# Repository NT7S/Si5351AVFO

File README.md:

# Si5351AVFO
Si5351A VFO board for the Si5351 Field Manual (Chapter 6).

## Regenerating docs

After any schematic change, run `tools/export_docs.sh` (needs KiCad 10 `kicad-cli`).
It rewrites `docs/Si5351AVFO_schematic.pdf`, the netlist, SVGs and `docs/erc.rpt`.

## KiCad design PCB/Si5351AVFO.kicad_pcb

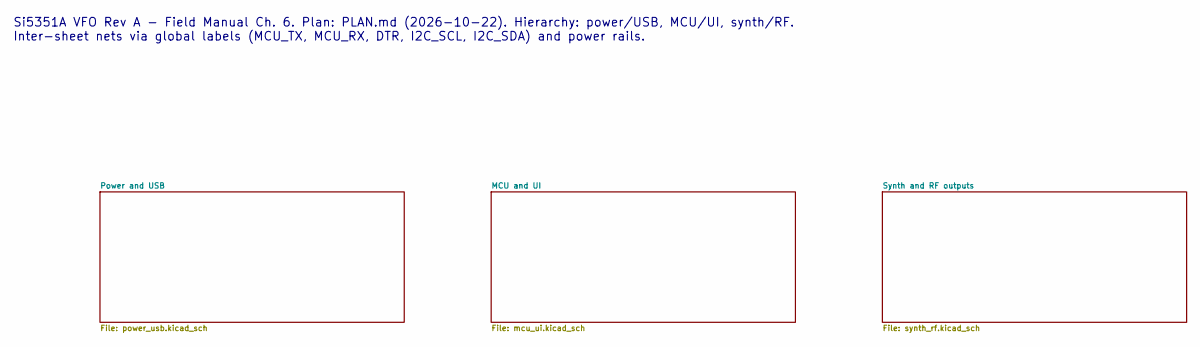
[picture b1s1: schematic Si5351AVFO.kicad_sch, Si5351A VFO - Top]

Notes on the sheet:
Si5351A VFO Rev A - Field Manual Ch. 6. Plan: PLAN.md (2026-10-22). Hierarchy: power/USB, MCU/UI, synth/RF. Inter-sheet nets via global labels (MCU_TX, MCU_RX, DTR, I2C_SCL, I2C_SDA) and power rails.

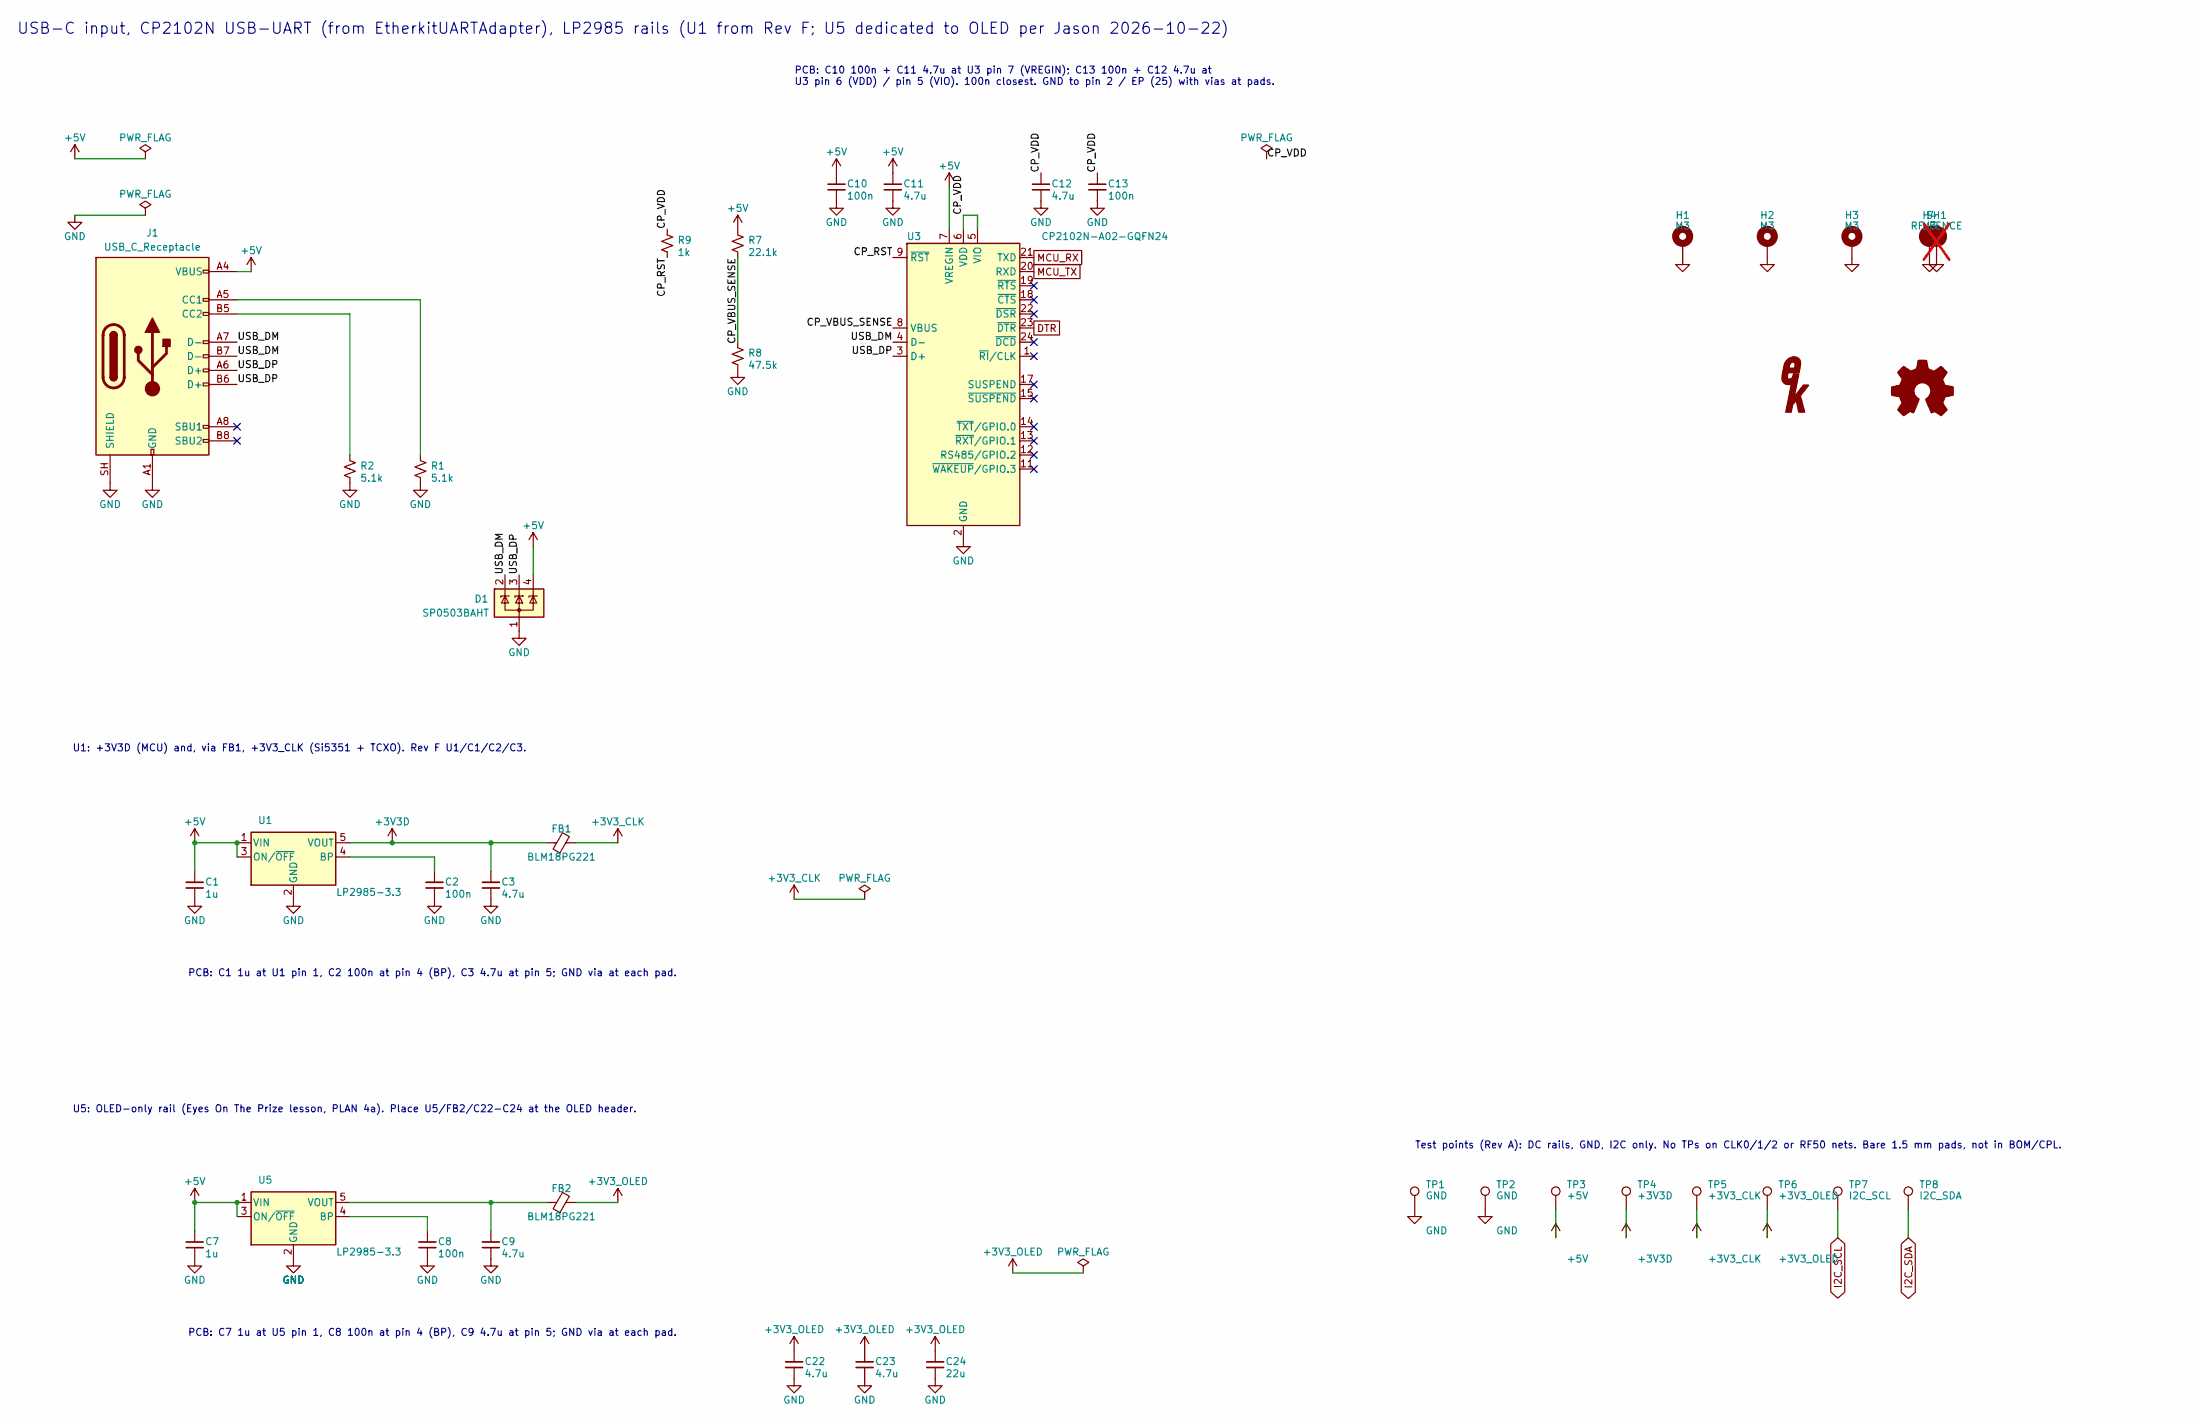
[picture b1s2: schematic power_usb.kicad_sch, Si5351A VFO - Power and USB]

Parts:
C1, C7: 1u; C_0805_2012Metric; MPN CL21B105KBFNNNE; LCSC C28323
C2, C8: 100n; C_0805_2012Metric; MPN CC0805KRX7R9BB104; LCSC C49678
C3, C9, C22, C23: 4.7u; C_0805_2012Metric; MPN CL21A475KAQNNNE; LCSC C1779
C10, C13: 100n; C_0603_1608Metric; MPN CC0603KRX7R9BB104; LCSC C14663
C11, C12: 4.7u; C_0603_1608Metric; MPN CL10A475KO8NNNC; LCSC C19666
C24: 22u; C_1206_3216Metric; MPN CL31A226KAHNNNE; LCSC C12891
D1: SP0503BAHT; SOT-143; MPN SP0503BAHTG; LCSC C7074
FB1, FB2: BLM18PG221; L_0603_1608Metric; MPN BLM18PG221SN1D; LCSC C80165
H1, H2, H3, H4: M3; MountingHole_3.2mm_M3_Pad_Via
J1: USB_C_Receptacle; USB_C_Receptacle_HCTL_HC-TYPE-C-16P-01A; MPN HC-TYPE-C-16P-01A; LCSC C2894897
R1, R2: 5.1k; R_0603_1608Metric; MPN 0603WAF5101T5E; LCSC C23186
R7: 22.1k; R_0603_1608Metric; MPN RC0603FR-0722K1L; LCSC C137768
R8: 47.5k; R_0603_1608Metric; MPN FRC0603F4752TS; LCSC C2933225
R9: 1k; R_0603_1608Metric; MPN 0603WAF1001T5E; LCSC C21190
SH1: RF_FENCE; RF_Fence_42x33.5mm; not fitted
TP1, TP2: GND; TestPoint_Pad_D1.5mm
TP3: +5V; TestPoint_Pad_D1.5mm
TP4: +3V3D; TestPoint_Pad_D1.5mm
TP5: +3V3_CLK; TestPoint_Pad_D1.5mm
TP6: +3V3_OLED; TestPoint_Pad_D1.5mm
TP7: I2C_SCL; TestPoint_Pad_D1.5mm
TP8: I2C_SDA; TestPoint_Pad_D1.5mm
U1, U5: LP2985-3.3; SOT-23-5; MPN LP2985AIM5-3.3/NOPB; LCSC C16085
U3: CP2102N-A02-GQFN24; QFN-24-1EP_4x4mm_P0.5mm_EP2.6x2.6mm; MPN CP2102N-A02-GQFN24R; LCSC C969151

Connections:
+3V3D: C3.1, FB1.1, TP4.1, U1.5 (VOUT); also elsewhere on the board
+3V3_CLK: FB1.2, TP5.1; also elsewhere on the board
+3V3_OLED: C22.1, C23.1, C24.1, FB2.2, TP6.1; also elsewhere on the board
+5V: C1.1, C7.1, C10.1, C11.1, D1.4 (K), J1.A4 (VBUS), J1.A9 (VBUS), J1.B4 (VBUS), J1.B9 (VBUS), R7.1, TP3.1, U1.1 (VIN), U1.3 (ON/~OFF), U3.7 (VREGIN), U5.1 (VIN), U5.3 (ON/~OFF)
/Power and USB/CP_RST: R9.2, U3.9 (~RST)
/Power and USB/CP_VBUS_SENSE: R7.2, R8.1, U3.8 (VBUS)
/Power and USB/CP_VDD: C12.1, C13.1, R9.1, U3.5 (VIO), U3.6 (VDD)
/Power and USB/USB_DM: D1.2 (K), J1.A7 (D-), J1.B7 (D-), U3.4 (D-)
/Power and USB/USB_DP: D1.3 (K), J1.A6 (D+), J1.B6 (D+), U3.3 (D+)
DTR: U3.23 (~DTR); also elsewhere on the board
GND: C1.2, C2.2, C3.2, C7.2, C8.2, C9.2, C10.2, C11.2, C12.2, C13.2, C22.2, C23.2, C24.2, D1.1 (A), H1.1, H2.1, H3.1, H4.1, J1.A1 (GND), J1.A12 (GND), J1.B1 (GND), J1.B12 (GND), J1.SH (SHIELD), R1.2, R2.2, R8.2, SH1.1, TP1.1, TP2.1, U1.2 (GND), U3.2 (GND), U3.25 (GND), U5.2 (GND); also elsewhere on the board
I2C_SCL: TP7.1; also elsewhere on the board
I2C_SDA: TP8.1; also elsewhere on the board
MCU_RX: U3.21 (TXD); also elsewhere on the board
MCU_TX: U3.20 (RXD); also elsewhere on the board
unnamed: J1.A5 (CC1), R1.1
unnamed: J1.B5 (CC2), R2.1
unnamed: C2.1, U1.4 (BP)
unnamed: C8.1, U5.4 (BP)
unnamed: C9.1, FB2.1, U5.5 (VOUT)

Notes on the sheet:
U1: +3V3D (MCU) and, via FB1, +3V3_CLK (Si5351 + TCXO). Rev F U1/C1/C2/C3.
USB-C input, CP2102N USB-UART (from EtherkitUARTAdapter), LP2985 rails (U1 from Rev F; U5 dedicated to OLED per Jason 2026-10-22)
U5: OLED-only rail (Eyes On The Prize lesson, PLAN 4a). Place U5/FB2/C22-C24 at the OLED header.
PCB: C10 100n + C11 4.7u at U3 pin 7 (VREGIN); C13 100n + C12 4.7u at U3 pin 6 (VDD) / pin 5 (VIO). 100n closest. GND to pin 2 / EP (25) with vias at pads.
PCB: C1 1u at U1 pin 1, C2 100n at pin 4 (BP), C3 4.7u at pin 5; GND via at each pad.
PCB: C7 1u at U5 pin 1, C8 100n at pin 4 (BP), C9 4.7u at pin 5; GND via at each pad.
Test points (Rev A): DC rails, GND, I2C only. No TPs on CLK0/1/2 or RF50 nets. Bare 1.5 mm pads, not in BOM/CPL.

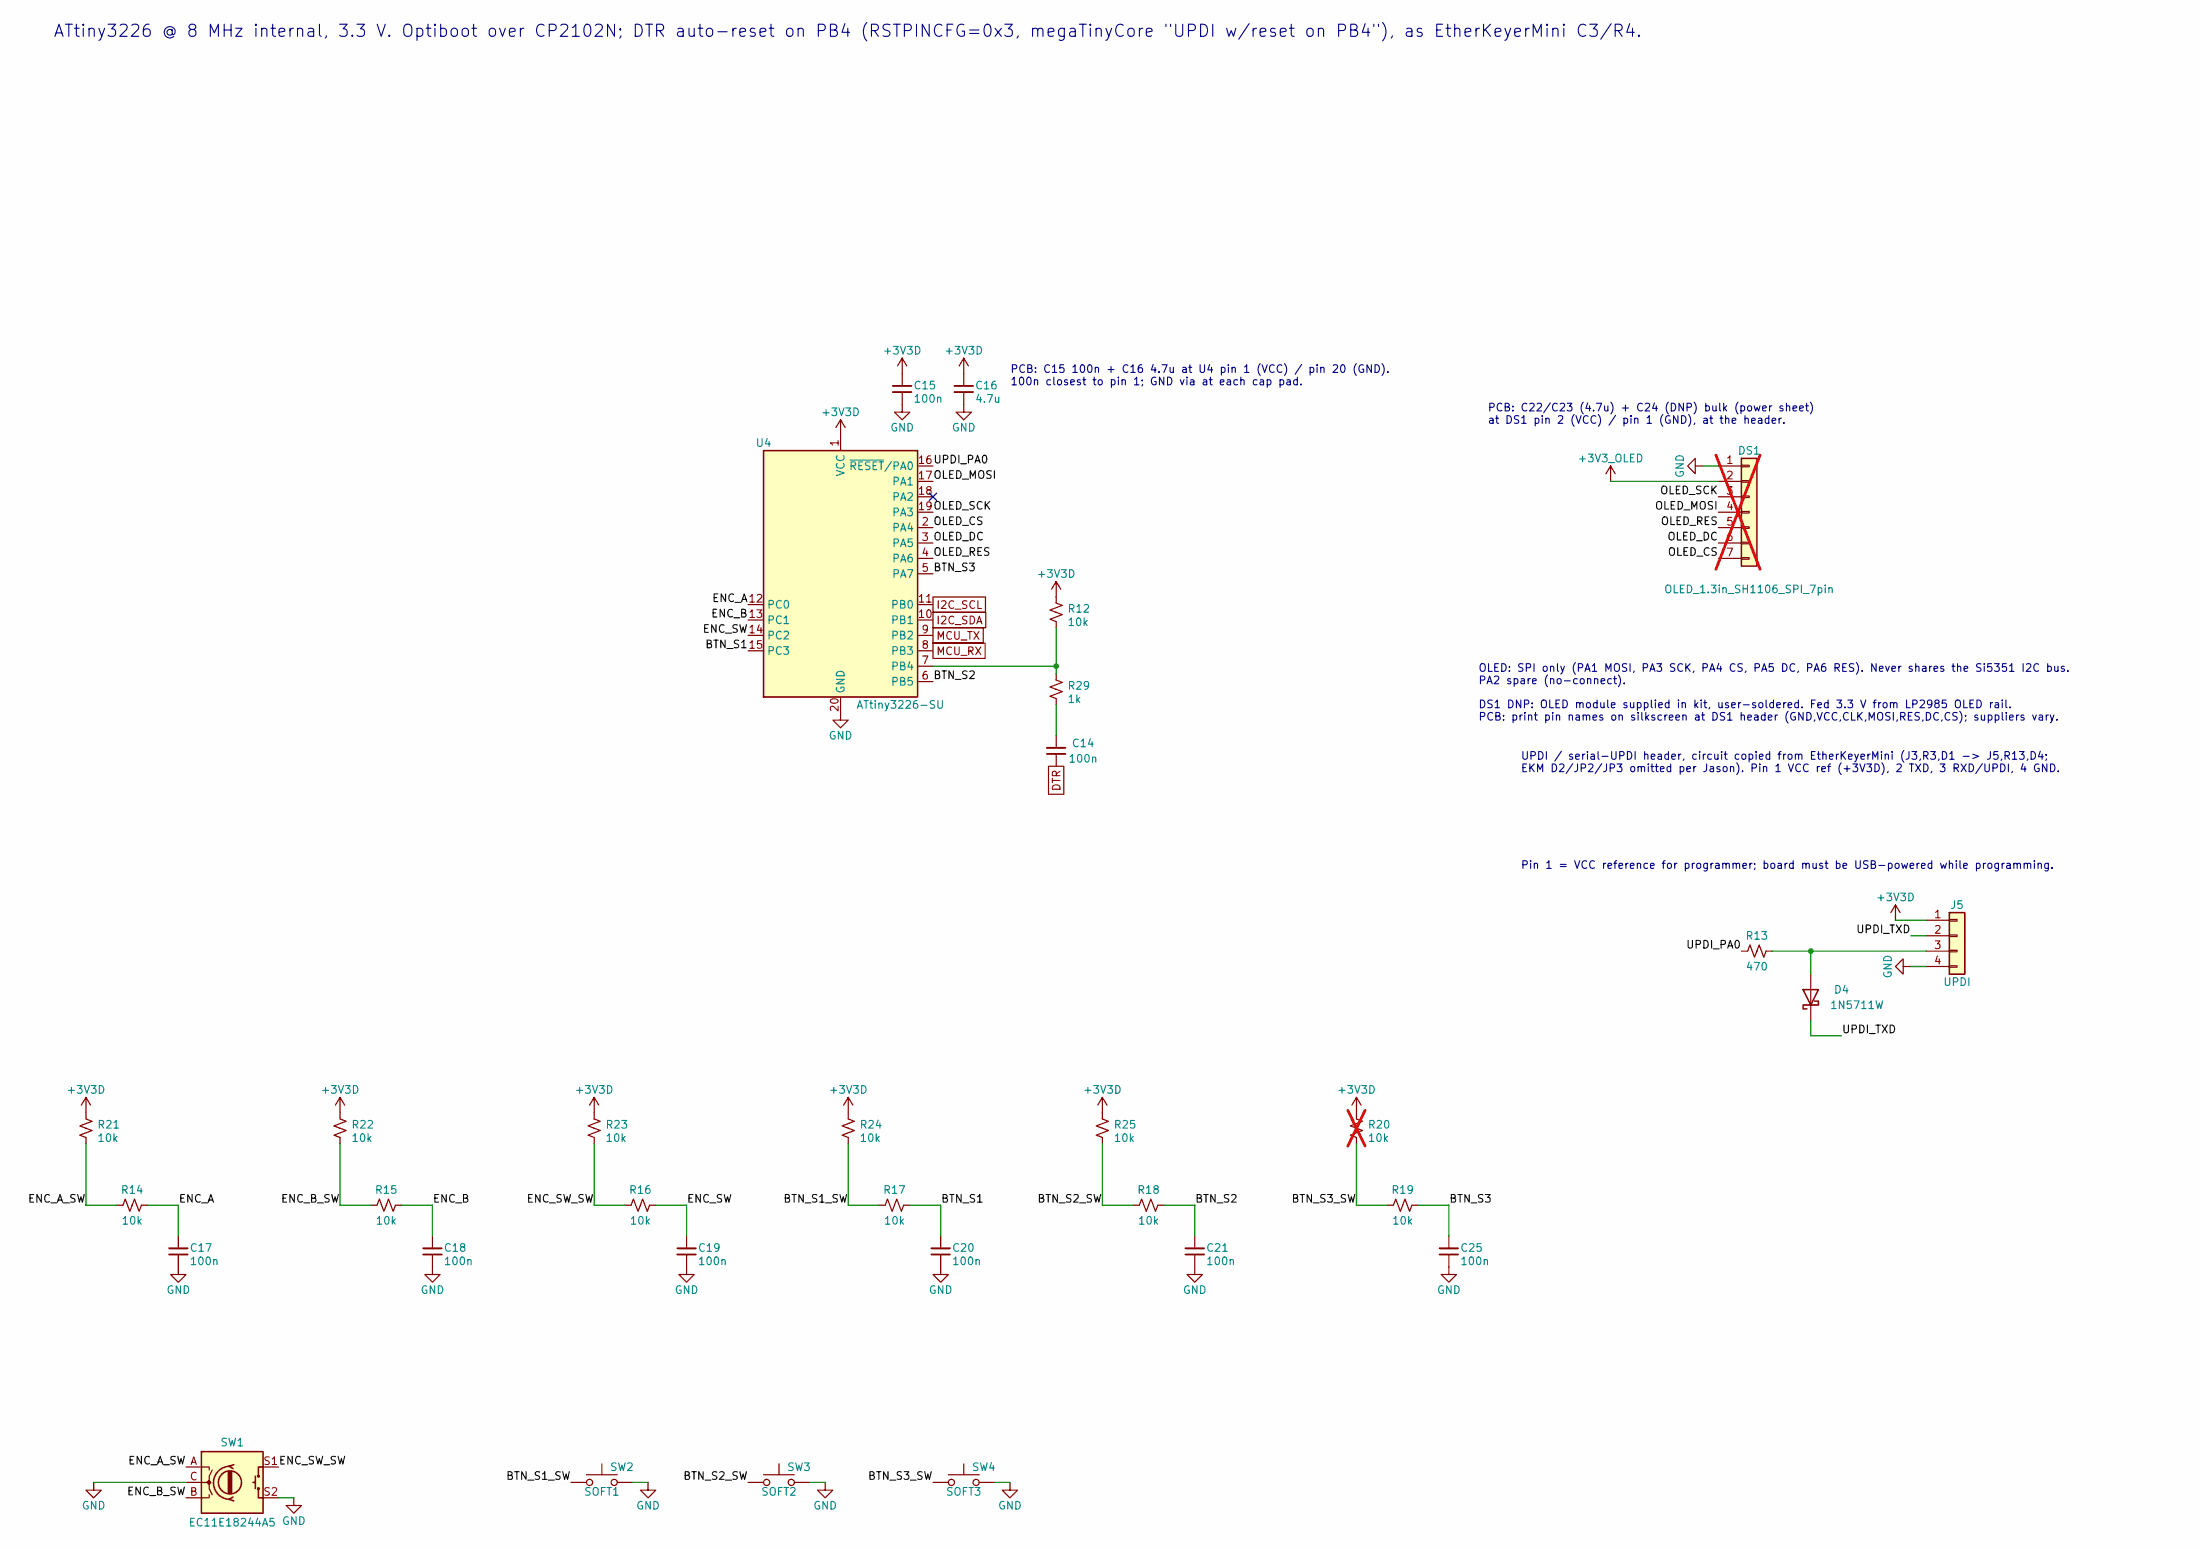
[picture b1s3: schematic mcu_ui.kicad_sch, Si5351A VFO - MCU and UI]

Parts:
C14, C15, C17, C18, C19, C20, C21, C25: 100n; C_0805_2012Metric; MPN CC0805KRX7R9BB104; LCSC C49678
C16: 4.7u; C_0805_2012Metric; MPN CL21A475KAQNNNE; LCSC C1779
D4: 1N5711W; D_SOD-123; MPN 1N5711W-7-F; LCSC C154843
DS1: OLED_1.3in_SH1106_SPI_7pin; PinHeader_1x07_P2.54mm_Vertical; MPN generic 1.3in SH1106 SPI 7-pin; not fitted
J5: UPDI; PinHeader_1x04_P2.54mm_Vertical; MPN B-2100S04P-A110; LCSC C124378
R12, R14, R15, R16, R17, R18, R19, R21, R22, R23, R24, R25: 10k; R_0805_2012Metric; MPN 0805W8F1002T5E; LCSC C17414
R13: 470; R_0603_1608Metric; MPN 0603WAF4700T5E; LCSC C23179
R20: 10k; R_0805_2012Metric; MPN 0805W8F1002T5E; LCSC C17414; not fitted
R29: 1k; R_0603_1608Metric; MPN 0603WAF1001T5E; LCSC C21190
SW1: EC11E18244A5; RotaryEncoder_Alps_EC11E-Switch_Vertical_H20mm; MPN EC11E18244A5; LCSC C255515
SW2: SOFT1; SW_Push_6x6mm_SMD_KH-6X6X11H-STM; MPN KH-6X6X11H-STM; LCSC C2837537
SW3: SOFT2; SW_Push_6x6mm_SMD_KH-6X6X11H-STM; MPN KH-6X6X11H-STM; LCSC C2837537
SW4: SOFT3; SW_Push_6x6mm_SMD_KH-6X6X11H-STM; MPN KH-6X6X11H-STM; LCSC C2837537
U4: ATtiny3226-SU; SOIC-20W_7.5x12.8mm_P1.27mm; MPN ATTINY3226-SU; LCSC C3234898

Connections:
+3V3D: C15.1, C16.1, J5.1, R12.1, R20.1, R21.1, R22.1, R23.1, R24.1, R25.1, U4.1 (VCC); also elsewhere on the board
+3V3_OLED: DS1.2; also elsewhere on the board
/MCU and UI/BTN_S1: C20.1, R17.2, U4.15 (PC3)
/MCU and UI/BTN_S1_SW: R17.1, R24.2, SW2.1
/MCU and UI/BTN_S2: C21.1, R18.2, U4.6 (PB5)
/MCU and UI/BTN_S2_SW: R18.1, R25.2, SW3.1
/MCU and UI/BTN_S3: C25.1, R19.2, U4.5 (PA7)
/MCU and UI/BTN_S3_SW: R19.1, R20.2, SW4.1
/MCU and UI/ENC_A: C17.1, R14.2, U4.12 (PC0)
/MCU and UI/ENC_A_SW: R14.1, R21.2, SW1.A
/MCU and UI/ENC_B: C18.1, R15.2, U4.13 (PC1)
/MCU and UI/ENC_B_SW: R15.1, R22.2, SW1.B
/MCU and UI/ENC_SW: C19.1, R16.2, U4.14 (PC2)
/MCU and UI/ENC_SW_SW: R16.1, R23.2, SW1.S1
/MCU and UI/OLED_CS: DS1.7, U4.2 (PA4)
/MCU and UI/OLED_DC: DS1.6, U4.3 (PA5)
/MCU and UI/OLED_MOSI: DS1.4, U4.17 (PA1)
/MCU and UI/OLED_RES: DS1.5, U4.4 (PA6)
/MCU and UI/OLED_SCK: DS1.3, U4.19 (PA3)
/MCU and UI/UPDI_PA0: R13.1, U4.16 (~RESET/PA0)
/MCU and UI/UPDI_TXD: D4.1 (K), J5.2
DTR: C14.1; also elsewhere on the board
GND: C15.2, C16.2, C17.2, C18.2, C19.2, C20.2, C21.2, C25.2, DS1.1, J5.4, SW1.C, SW1.S2, SW2.2, SW3.2, SW4.2, U4.20 (GND); also elsewhere on the board
I2C_SCL: U4.11 (PB0); also elsewhere on the board
I2C_SDA: U4.10 (PB1); also elsewhere on the board
MCU_RX: U4.8 (PB3); also elsewhere on the board
MCU_TX: U4.9 (PB2); also elsewhere on the board
unnamed: C14.2, R29.2
unnamed: D4.2 (A), J5.3, R13.2
unnamed: R12.2, R29.1, U4.7 (PB4)

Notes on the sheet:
UPDI / serial-UPDI header, circuit copied from EtherKeyerMini (J3,R3,D1 -> J5,R13,D4; EKM D2/JP2/JP3 omitted per Jason). Pin 1 VCC ref (+3V3D), 2 TXD, 3 RXD/UPDI, 4 GND.
OLED: SPI only (PA1 MOSI, PA3 SCK, PA4 CS, PA5 DC, PA6 RES). Never shares the Si5351 I2C bus. PA2 spare (no-connect).
DS1 DNP: OLED module supplied in kit, user-soldered. Fed 3.3 V from LP2985 OLED rail. PCB: print pin names on silkscreen at DS1 header (GND,VCC,CLK,MOSI,RES,DC,CS); suppliers vary.
ATtiny3226 @ 8 MHz internal, 3.3 V. Optiboot over CP2102N; DTR auto-reset on PB4 (RSTPINCFG=0x3, megaTinyCore "UPDI w/reset on PB4"), as EtherKeyerMini C3/R4.
Pin 1 = VCC reference for programmer; board must be USB-powered while programming.
PCB: C15 100n + C16 4.7u at U4 pin 1 (VCC) / pin 20 (GND). 100n closest to pin 1; GND via at each cap pad.
PCB: C22/C23 (4.7u) + C24 (DNP) bulk (power sheet) at DS1 pin 2 (VCC) / pin 1 (GND), at the header.

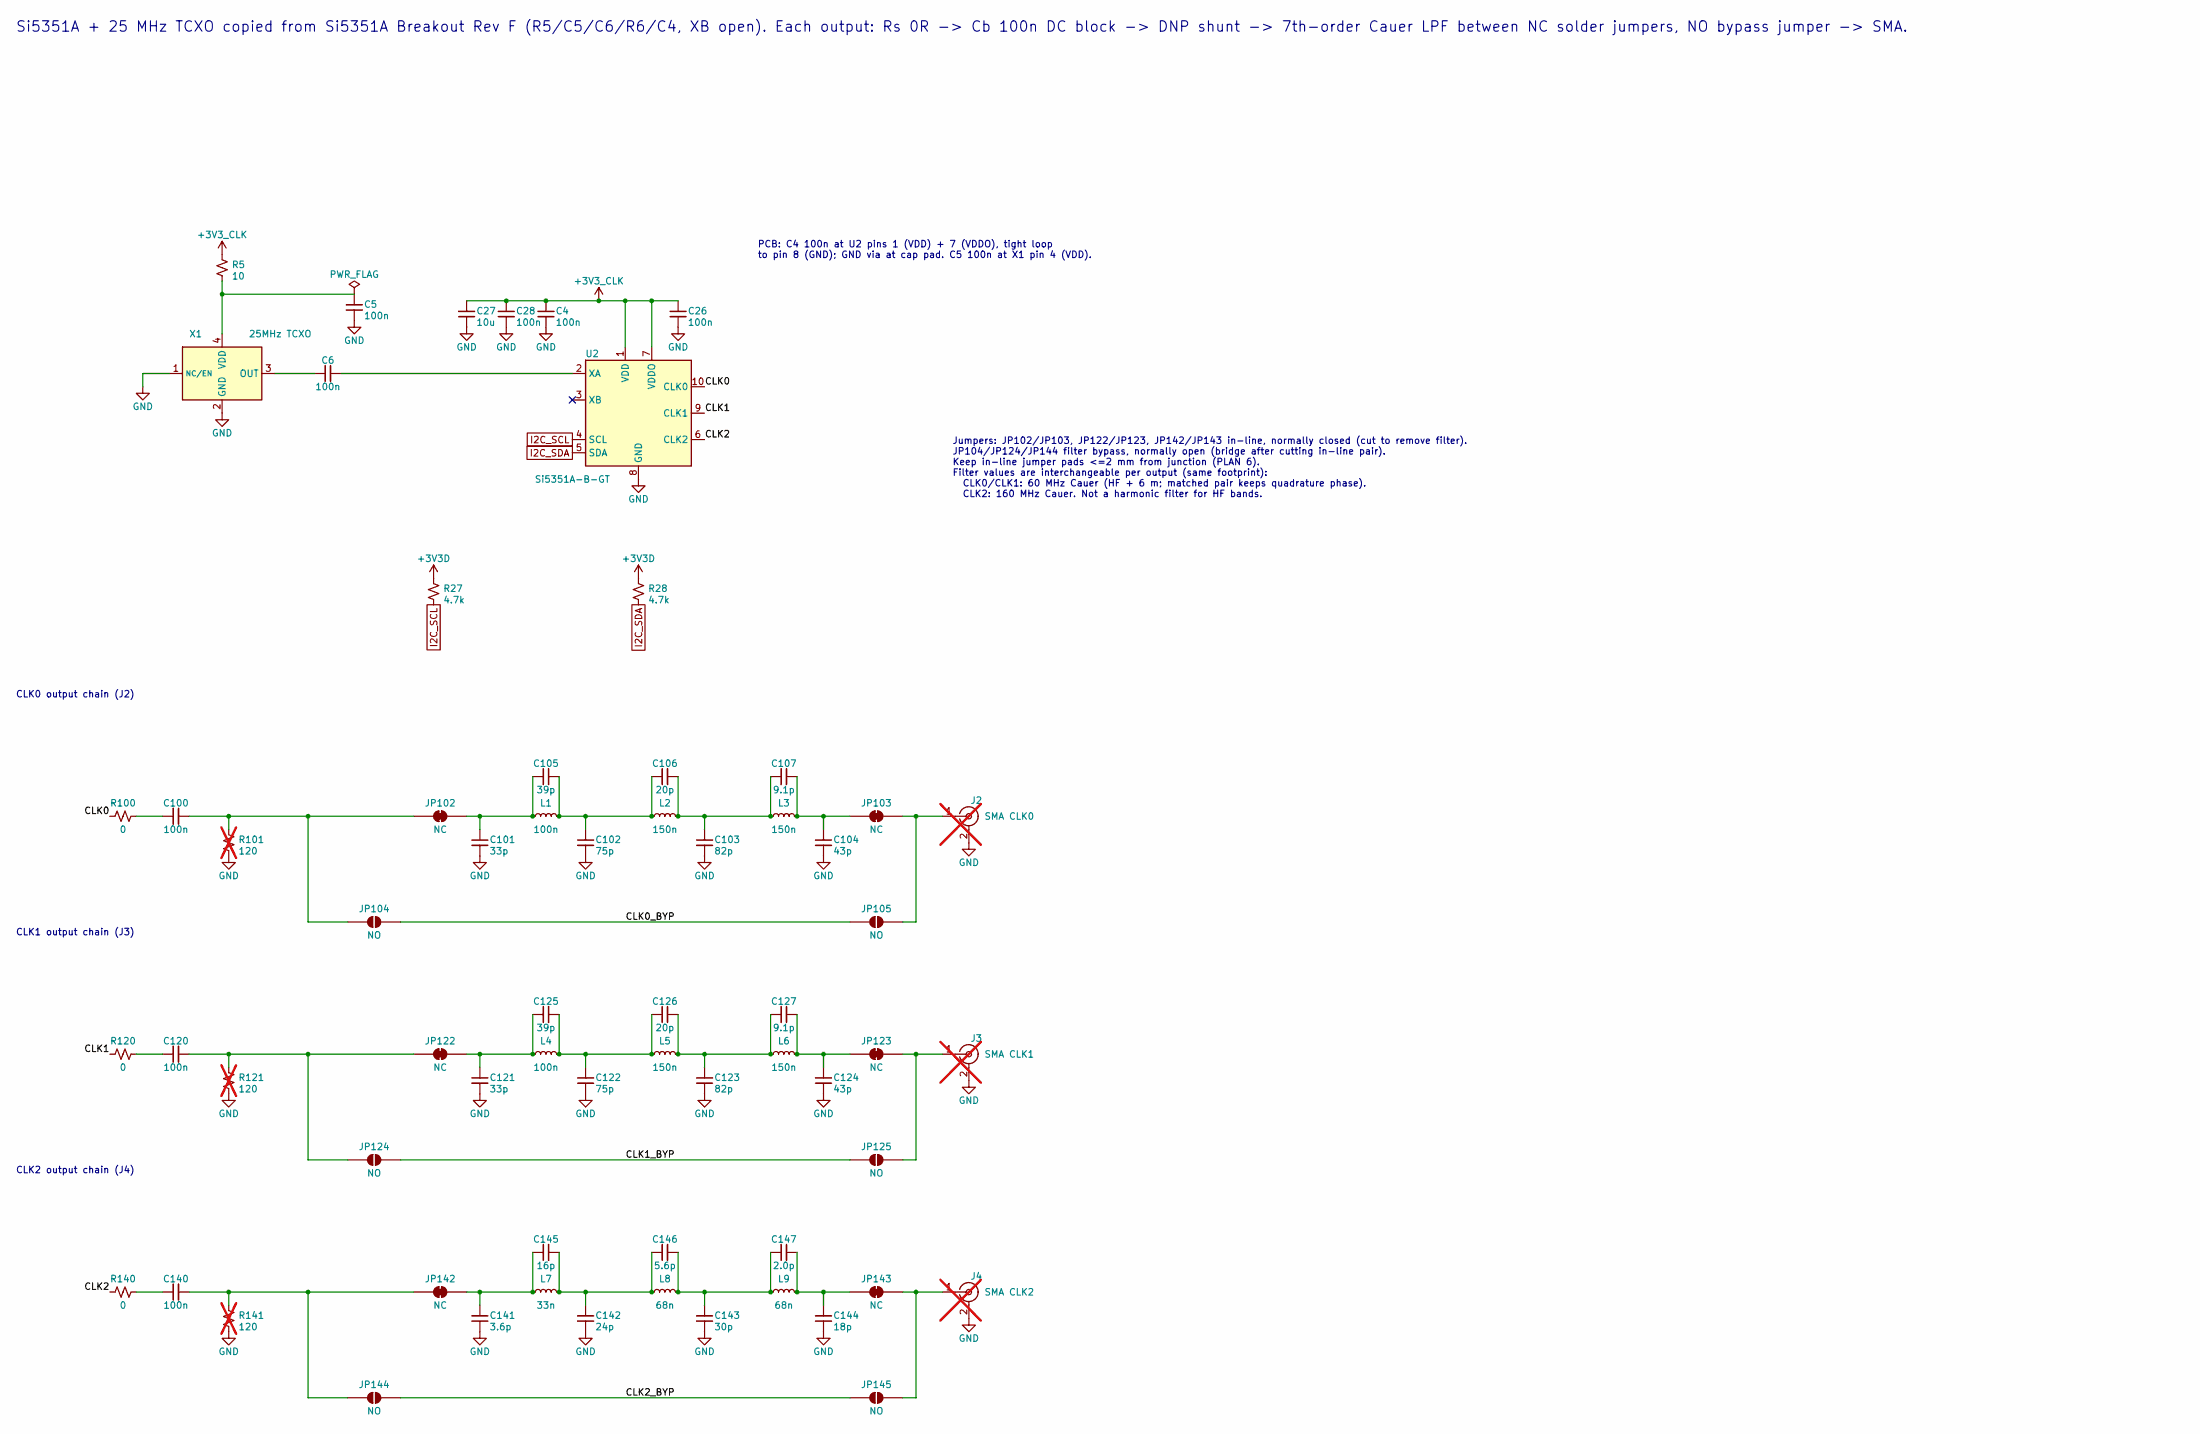
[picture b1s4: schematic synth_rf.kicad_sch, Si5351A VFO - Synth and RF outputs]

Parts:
C4, C5, C6, C28, C100, C120, C140: 100n; C_0805_2012Metric; MPN CC0805KRX7R9BB104; LCSC C49678
C26: 100n; C_0402_1005Metric; MPN CL05B104KO5NNNC; LCSC C1525
C27: 10u; C_0805_2012Metric; MPN CL21A106KAYNNNE; LCSC C15850
C101, C121: 33p; C_0603_1608Metric; MPN CC0603FRNPO9BN330; LCSC C519485
C102, C122: 75p; C_0603_1608Metric; MPN CC0603FRNPO9BN750; LCSC C519496
C103, C123: 82p; C_0603_1608Metric; MPN CC0603FRNPO9BN820; LCSC C519487
C104, C124: 43p; C_0603_1608Metric; MPN CC0603FRNPO9BN430; LCSC C519493
C105, C125: 39p; C_0603_1608Metric; MPN CC0603FRNPO9BN390; LCSC C527048
C106, C126: 20p; C_0603_1608Metric; MPN CC0603FRNPO9BN200; LCSC C326779
C107, C127: 9.1p; C_0603_1608Metric; MPN CC0603CRNPO9BN9R1; LCSC C513588
C141: 3.6p; C_0603_1608Metric; MPN CC0603BRNPO9BN3R6; LCSC C519106
C142: 24p; C_0603_1608Metric; MPN 0603CG240G500NT; LCSC C2857979
C143: 30p; C_0603_1608Metric; MPN CC0603FRNPO9BN300; LCSC C519491
C144: 18p; C_0603_1608Metric; MPN CC0603FRNPO9BN180; LCSC C527046
C145: 16p; C_0603_1608Metric; MPN CC0603FRNPO9BN160; LCSC C519489
C146: 5.6p; C_0603_1608Metric; MPN CC0603BRNPO9BN5R6; LCSC C519111
C147: 2.0p; C_0603_1608Metric; MPN CC0603BRNPO9BN2R0; LCSC C513620
J2: SMA CLK0; SMA-ENDLAUNCH; MPN BWSMA-KE-P001; not fitted
J3: SMA CLK1; SMA-ENDLAUNCH; MPN BWSMA-KE-P001; not fitted
J4: SMA CLK2; SMA-ENDLAUNCH; MPN BWSMA-KE-P001; not fitted
JP102, JP103, JP122, JP123, JP142, JP143: NC; SolderJumper-2_P1.3mm_Bridged_RoundedPad1.0x1.5mm
JP104, JP105, JP124, JP125, JP144, JP145: NO; SolderJumper-2_P1.3mm_Open_RoundedPad1.0x1.5mm
L1, L4: 100n; L_1008_2520Metric; MPN LQW2UASR10G0CL; LCSC C1330579
L2, L3, L5, L6: 150n; L_1008_2520Metric; MPN LQW2UASR15F00L; LCSC C2044861
L7: 33n; L_1008_2520Metric; MPN LQW2UAS33NG0CL; LCSC C2043161
L8, L9: 68n; L_1008_2520Metric; MPN LQW2UAS68NG00L; LCSC C703709
R5: 10; R_0805_2012Metric; MPN 0805W8F100JT5E; LCSC C17415
R27, R28: 4.7k; R_0805_2012Metric; MPN 0805W8F4701T5E; LCSC C17673
R100, R120, R140: 0; R_0402_1005Metric; MPN 0402WGF0000TCE; LCSC C17168
R101, R121, R141: 120; R_0805_2012Metric; MPN 0805W8F1200T5E; LCSC C17437; not fitted
U2: Si5351A-B-GT; MSOP-10_3x3mm_P0.5mm; MPN SI5351A-B-GT; LCSC C529366
X1: 25MHz TCXO; Oscillator_SMD_SeikoEpson_SG8002CE-4Pin_3.2x2.5mm; MPN OW2EL89CENUXK7YLC-25M; LCSC C48888230

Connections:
+3V3D: R27.1, R28.1; also elsewhere on the board
+3V3_CLK: C4.1, C26.1, C27.1, C28.1, R5.1, U2.1 (VDD), U2.7 (VDDO); also elsewhere on the board
/Synth and RF outputs/CLK0: R100.1, U2.10 (CLK0)
/Synth and RF outputs/CLK0_BYP: JP104.2 (B), JP105.1 (A)
/Synth and RF outputs/CLK1: R120.1, U2.9 (CLK1)
/Synth and RF outputs/CLK1_BYP: JP124.2 (B), JP125.1 (A)
/Synth and RF outputs/CLK2: R140.1, U2.6 (CLK2)
/Synth and RF outputs/CLK2_BYP: JP144.2 (B), JP145.1 (A)
GND: C4.2, C5.2, C26.2, C27.2, C28.2, C101.2, C102.2, C103.2, C104.2, C121.2, C122.2, C123.2, C124.2, C141.2, C142.2, C143.2, C144.2, J2.2 (Ext), J3.2 (Ext), J4.2 (Ext), R101.2, R121.2, R141.2, U2.8 (GND), X1.1 (NC/EN), X1.2 (GND); also elsewhere on the board
I2C_SCL: R27.2, U2.4 (SCL); also elsewhere on the board
I2C_SDA: R28.2, U2.5 (SDA); also elsewhere on the board
unnamed: C100.1, R100.2
unnamed: C102.1, C105.2, C106.1, L1.2, L2.1
unnamed: C103.1, C106.2, C107.1, L2.2, L3.1
unnamed: C120.1, R120.2
unnamed: C122.1, C125.2, C126.1, L4.2, L5.1
unnamed: C123.1, C126.2, C127.1, L5.2, L6.1
unnamed: C140.1, R140.2
unnamed: C142.1, C145.2, C146.1, L7.2, L8.1
unnamed: C143.1, C146.2, C147.1, L8.2, L9.1
unnamed: J2.1 (In), JP103.2 (B), JP105.2 (B)
unnamed: J3.1 (In), JP123.2 (B), JP125.2 (B)
unnamed: J4.1 (In), JP143.2 (B), JP145.2 (B)
unnamed: C100.2, JP102.1 (A), JP104.1 (A), R101.1
unnamed: C101.1, C105.1, JP102.2 (B), L1.1
unnamed: C104.1, C107.2, JP103.1 (A), L3.2
unnamed: C120.2, JP122.1 (A), JP124.1 (A), R121.1
unnamed: C121.1, C125.1, JP122.2 (B), L4.1
unnamed: C124.1, C127.2, JP123.1 (A), L6.2
unnamed: C140.2, JP142.1 (A), JP144.1 (A), R141.1
unnamed: C141.1, C145.1, JP142.2 (B), L7.1
unnamed: C144.1, C147.2, JP143.1 (A), L9.2
unnamed: C6.2, U2.2 (XA)
unnamed: C6.1, X1.3 (OUT)
unnamed: C5.1, R5.2, X1.4 (VDD)

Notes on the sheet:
CLK0 output chain (J2)
Si5351A + 25 MHz TCXO copied from Si5351A Breakout Rev F (R5/C5/C6/R6/C4, XB open). Each output: Rs 0R -> Cb 100n DC block -> DNP shunt -> 7th-order Cauer LPF between NC solder jumpers, NO bypass jumper -> SMA.
CLK2 output chain (J4)
CLK1 output chain (J3)
Jumpers: JP102/JP103, JP122/JP123, JP142/JP143 in-line, normally closed (cut to remove filter). JP104/JP124/JP144 filter bypass, normally open (bridge after cutting in-line pair). Keep in-line jumper pads <=2 mm from junction (PLAN 6). Filter values are interchangeable per output (same footprint): 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
PCB: C4 100n at U2 pins 1 (VDD) + 7 (VDDO), tight loop to pin 8 (GND); GND via at cap pad. C5 100n at X1 pin 4 (VDD).

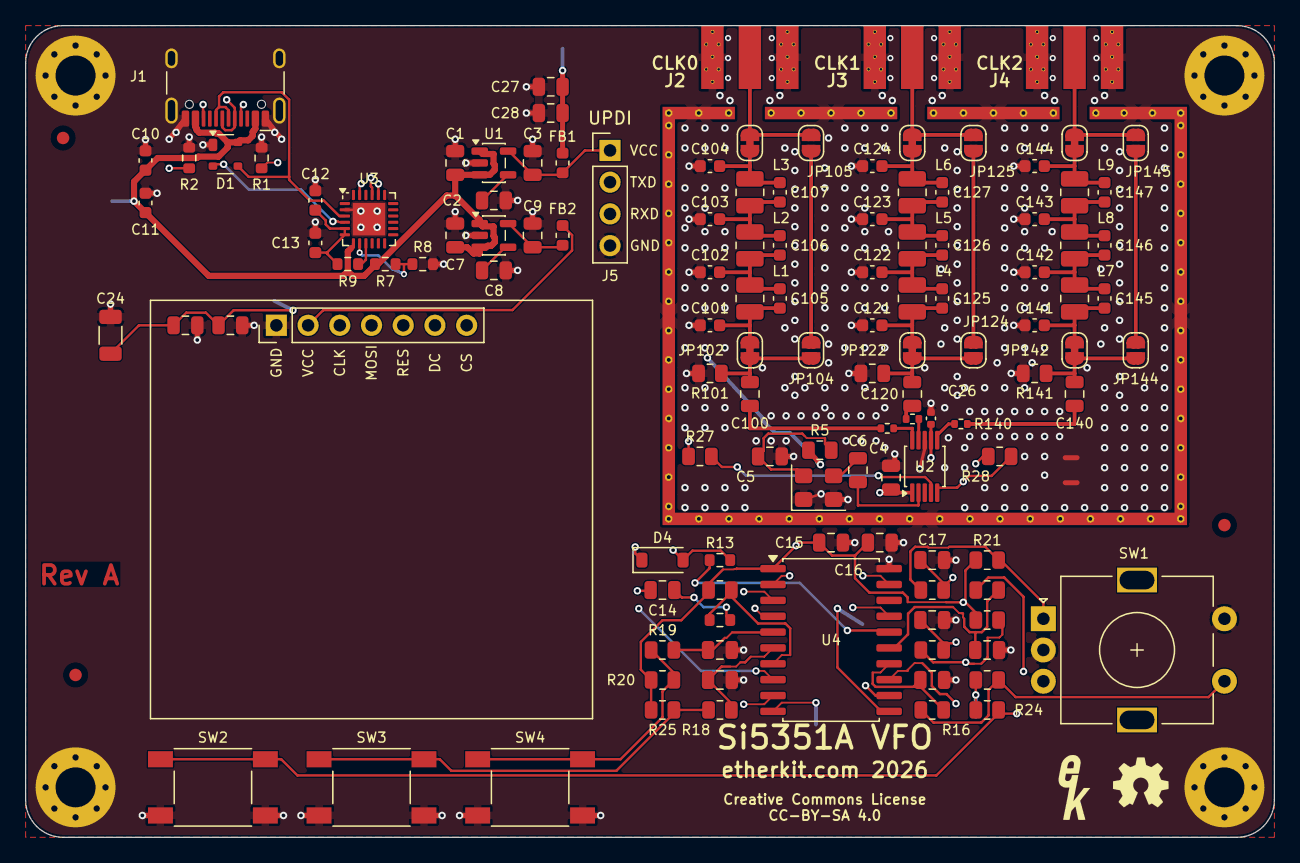
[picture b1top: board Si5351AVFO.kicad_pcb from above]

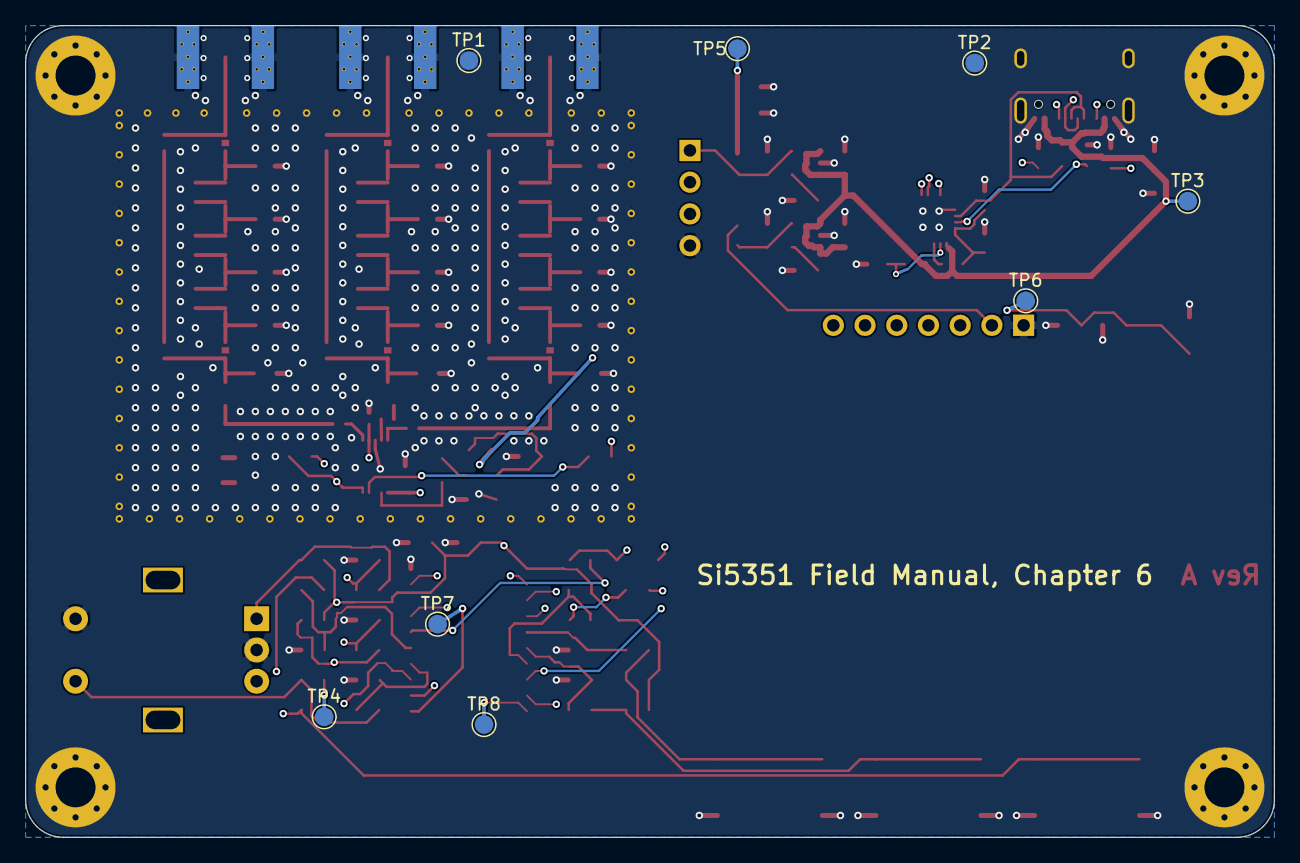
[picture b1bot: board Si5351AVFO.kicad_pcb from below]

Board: 4 copper layers, 100.0 x 65.0 mm, 140 parts (8 on the bottom side), 72 nets.

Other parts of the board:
FID1, FID2, FID3: Fiducial; Fiducial_1mm_Mask2mm
LOGO1: Val**; EtherkitLogoSmall
LOGO2: Logo_Open_Hardware_Small; OSHWLogo4mm

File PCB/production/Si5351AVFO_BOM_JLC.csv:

Comment,Designator,Footprint,LCSC Part #
1u,"C1,C7",C_0805_2012Metric,C28323
100n,"C2,C4-C6,C8,C14,C15,C17-C21,C25,C28,C100,C120,C140",C_0805_2012Metric,C49678
4.7u,"C3,C9,C16,C22,C23",C_0805_2012Metric,C1779
100n,"C10,C13",C_0603_1608Metric,C14663
4.7u,"C11,C12",C_0603_1608Metric,C19666
22u,C24,C_1206_3216Metric,C12891
100n,C26,C_0402_1005Metric,C1525
10u,C27,C_0805_2012Metric,C15850
33p,"C101,C121",C_0603_1608Metric,C519485
75p,"C102,C122",C_0603_1608Metric,C519496
82p,"C103,C123",C_0603_1608Metric,C519487
43p,"C104,C124",C_0603_1608Metric,C519493
39p,"C105,C125",C_0603_1608Metric,C527048
20p,"C106,C126",C_0603_1608Metric,C326779
9.1p,"C107,C127",C_0603_1608Metric,C513588
3.6p,C141,C_0603_1608Metric,C519106
24p,C142,C_0603_1608Metric,C2857979
30p,C143,C_0603_1608Metric,C519491
18p,C144,C_0603_1608Metric,C527046
16p,C145,C_0603_1608Metric,C519489
5.6p,C146,C_0603_1608Metric,C519111
2.0p,C147,C_0603_1608Metric,C513620
SP0503BAHT,D1,SOT-143,C7074
1N5711W,D4,D_SOD-123,C154843
BLM18PG221,"FB1,FB2",L_0603_1608Metric,C80165
USB_C_Receptacle,J1,USB_C_Receptacle_HCTL_HC-TYPE-C-16P-01A,C2894897
UPDI,J5,PinHeader_1x04_P2.54mm_Vertical,C124378
100n,"L1,L4",L_1008_2520Metric,C1330579
150n,"L2,L3,L5,L6",L_1008_2520Metric,C2044861
33n,L7,L_1008_2520Metric,C2043161
68n,"L8,L9",L_1008_2520Metric,C703709
5.1k,"R1,R2",R_0603_1608Metric,C23186
10,R5,R_0805_2012Metric,C17415
22.1k,R7,R_0603_1608Metric,C137768
47.5k,R8,R_0603_1608Metric,C2933225
1k,"R9,R29",R_0603_1608Metric,C21190
10k,"R12,R14-R19,R21-R25",R_0805_2012Metric,C17414
470,R13,R_0603_1608Metric,C23179
4.7k,"R27,R28",R_0805_2012Metric,C17673
0,"R100,R120,R140",R_0402_1005Metric,C17168
EC11E18244A5,SW1,RotaryEncoder_Alps_EC11E-Switch_Vertical_H20mm,C255515
SOFT1,SW2,SW_Push_6x6mm_SMD_KH-6X6X11H-STM,C2837537
SOFT2,SW3,SW_Push_6x6mm_SMD_KH-6X6X11H-STM,C2837537
SOFT3,SW4,SW_Push_6x6mm_SMD_KH-6X6X11H-STM,C2837537
LP2985-3.3,"U1,U5",SOT-23-5,C16085
Si5351A-B-GT,U2,MSOP-10_3x3mm_P0.5mm,C529366
CP2102N-A02-GQFN24,U3,QFN-24-1EP_4x4mm_P0.5mm_EP2.6x2.6mm,C969151
ATtiny3226-SU,U4,SOIC-20W_7.5x12.8mm_P1.27mm,C3234898
25MHz TCXO,X1,Oscillator_SMD_SeikoEpson_SG8002CE-4Pin_3.2x2.5mm,C48888230

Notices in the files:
PCB/Si5351AVFO.kicad_pcb:
Creative Commons License
CC-BY-SA 4.0
